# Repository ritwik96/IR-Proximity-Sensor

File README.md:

# IR-Proximity-Sensor
Tunable IR based proximity sensor with a digital output

<ul>
<li>Autodesk Eagle .brd and .sch files included with all non-standard libs</li>
<li>Sample Arduino code also for tuning and testing included</li>
<li>Potentiometer used to adjust the range</li>
<li>Detection range of about 9cm (3.5 in)</li>
</ul>
<p><strong>Important Notes:</strong></p>
<ul class="remarkup-list">
<li class="remarkup-list-item">The 220 &Omega; resistor is a pull-up in parallel with the LED. The LED needs to be one with an internal resistance (Standard RED 5mm LED with internal resistance is recommended)</li>
<li class="remarkup-list-item">The board has a normal HIGH and triggered LOW. The LED will be ON when the sensor hasn't been triggered and will turn OFF when it has.</li>
</ul>
<br>
<br>
<b> BOM: </b>
<table style="width: 340px;">
<tbody>
<tr>
<td style="width: 224px;">
<p><strong>Part</strong></p>
</td>
<td style="width: 90px;">
<p><strong>Part no.</strong></p>
</td>
<td style="width: 25px;">
<p><strong>Quantity</strong></p>
</td>
</tr>
<tr>
<td style="width: 224px;">
<p>IR Reflective Sensor</p>
</td>
<td style="width: 90px;">
<p>TCRT 5000</p>
</td>
<td style="width: 25px;">
<p>1</p>
</td>
</tr>
<tr>
<td style="width: 224px;">
<p>Red LED (internal resistor)</p>
</td>
<td style="width: 90px;">&nbsp;</td>
<td style="width: 25px;">
<p>1</p>
</td>
</tr>
<tr>
<td style="width: 224px;">
<p>100 ohm Resistor</p>
</td>
<td style="width: 90px;">&nbsp;</td>
<td style="width: 25px;">
<p>1</p>
</td>
</tr>
<tr>
<td style="width: 224px;">
<p>220 ohm Resistor</p>
</td>
<td style="width: 90px;">&nbsp;</td>
<td style="width: 25px;">
<p>1</p>
</td>
</tr>
<tr>
<td style="width: 224px;">
<p>4.7k ohm Resistor</p>
</td>
<td style="width: 90px;">&nbsp;</td>
<td style="width: 25px;">
<p>1</p>
</td>
</tr>
<tr>
<td style="width: 224px;">
<p>10k Multi-turn POT</p>
</td>
<td style="width: 90px;">&nbsp;</td>
<td style="width: 25px;">
<p>1</p>
</td>
</tr>
<tr>
<td style="width: 224px;">
<p>0.1uF Ceramic Capacitor</p>
</td>
<td style="width: 90px;">&nbsp;</td>
<td style="width: 25px;">
<p>2</p>
</td>
</tr>
<tr>
<td style="width: 224px;">
<p>TL081 op-amp</p>
</td>
<td style="width: 90px;">
<p>TL081</p>
</td>
<td style="width: 25px;">
<p>1</p>
</td>
</tr>
<tr>
<td style="width: 224px;">
<p>LM311N op-amp</p>
</td>
<td style="width: 90px;">
<p>LM311N</p>
</td>
<td style="width: 25px;">
<p>1</p>
</td>
</tr>
<tr>
<td style="width: 224px;">
<p>Break Away Headers</p>
</td>
<td style="width: 90px;">&nbsp;</td>
<td style="width: 25px;">
<p>6</p>
</td>
</tr>
</tbody>
</table>
<br>
<br>
<b> Schematic </b>
<p><img src="https://lh3.googleusercontent.com/fife/AAWUweXJ0cqJTT9yQKcJLtwWGiwWtPHNEDslHPKHX4X1kVe6rQgvylilLF-veRYypt4GBSyLvxIxgf_NBnjHtnxn2Fl2rCG9K_CXedOrj_bJrCb9PioXvAnjB80D2a0JiKlN0q2BV1EuuyBJM3cF4zWPFrK_ZCTCOgk6yfm_oHXbCRD5ekSx6PWZowFjhlelqWYi70vbxbF-7owTEbR0xGJ5UWBRVcrjVOpbwydnRtH584SyAf-udRqynxx5dkARvue_5rLb3AlWk1Whh5RAajTCkvgW4AK1EAxEA8O7RRdv5iY4lzVDs3q3AZRbzjtEcMSYzmWkkQL8p_EDrIesJH7LgoMswqbennmZJk6drwUTHa71WNQo625rHrt8JnTFp2NSJ6NUYdfE151DOkQJxdNym9DSvMmVbrnafRu51aJyEk-NZaPi9QqR9XVH6-emrRRxPwtjUv7AzXcPG-ChSayDAqQHkr3lHhr_HujkP6v8GJ7Ek8r4JnYpr-zAE-dVjSty9proRJBWXbD01yU5dkvpQ8BYxBlc7e2ec_te5tm6TB70sySlBcXVLOqPu8-fop8WtkFTbITsYDsc-INzU177CpvXsvYDvdM7-Vjdk6bKgADZnufWxZXwwVHX3nUWLGIkV43qQwWrHAA816nxQxJTwIUY5DzuLddsJ_GjRQXqQ61aT__i1tyuH3yLi4vK7uP3y0tMJPLedDnnJIhWBYNk91k-UWk83fL_AC7vRa7_l8D-C2yvENC-iwf1alsjptwYCByUk4cvoQbbeGjgenzsshzjy2SdnkBOlhW0RhNocaOOkBKnMzyLFkr0ULQ3GJD6mguxIJdqG7CRH68a-Pl1_XZ5OfUJI4QYMwJ18C_BT0NWODeldg-inMBEKxh29MLZ8zIS4MpJWytfc0aYgFdNBcCUETBavcrAqinttq3YfZGPw8WbIf54afK3jPAQjIfaGodGy0qtbEUKXmHyIePLx9rw3gC59Uip7NdncRc8NIJMqCAMtXVjI8OnZH58SrmUf0QIwZfzkkGyAQ264nmQQM5bM-25FlpJIfriYAnz6cHoLN6rQkTZCmzi7AUVCMAzfGevw9UFx7Adk3Q3j2fWAD78qvecGiyIZuXCTCXmhoCpCuhUNc9kRCWo-vuahQz9BENvtymh8kyJj-AwA9Niu45XOD043px8s4_OlvbjdNb-VAIlMGryZ3OectBs7BbqDaD0-c9xFugOCttM_4Tn2e-H8yTLttc1BWikI82273CD3G56k1ZH5o07MobdQc12tD5cWWRtP6IS_J6vC4gZEj-jM_8oDNllCH6MjUvSWEbnKAHjXu-avTNzrUCLkVz64DbCiiWOAUu60jM1AWN8OCly30CuyNWg2KreVKFh8v0ZTHyILAKf1MzP5oEXidUEEe-LI36NUuLEj9IOODJtNKK6oW2PpvOdvrH3tbwfAw5Af32BFiYyNrqu2490iqmG_BL2tslQMtXDjyu0mlZt9GxM8YzY6WgpfVl5zzp3Ih2lDolEXcSJTntM3rKIvmz7Bs_Khb9HHj3Y8v3xbcyiXVLvpdX2qNtXukv05Y8x05GDsp59mWwkrLJorkgG-Eh5kPmEPltWHlA2lcAxN1EQIZrs10f7ycuyMRtShH4vymmiTzteLxZle8fCAyBbxx_BmKJiU03YqFCQq2MoFFU43bGBEuxs20FnXFYBEQt2x9yrEJ94GQ16KcLWwIRsBsCuYT4ekjIKE8RHF7VOGT-ZcSkayg9mSYw3FODNxonVjNbYXlbvWIP0-sByOPo5AyfK6kWpGPndsg1T9ogEUTXN32a1CnleRyb_ccDMs5kaSVA_nfqZ7RreaXSj8PavfMwAv9ibYOmS0SjZ76zIcb0dIJC7D_SzT44zdXpMAAXEPWCfTBj6HfJVU3IbzwB8W1vevgtk9MoOuS0_nCHk6jJAUg4gvagi8ZMxVawoSxpBNMpRm28Lnk243cEJkULltNM3uga3nltLoyhNbtYhMlIXtQ7Uynx69zBnO-2WP8uNJpHhrF7ViGFTa2iSNq46iVgfaQIfewvbFprwMCFNRnXhkqi4X3cFJhdRqhqxQ4VhZ_7_kiT-fTb2esYIBMuvrr2P4dbOHbYCSA0XigmI8ZxShCH80p3EZVXWyqOzcscU1aXllhD9_zsxhFEfYV9_RS5KsZJbd3o2Ec1sdUKBxMyqP1GwGSXpZ4ZLdUcoTWYqwpNyDum7Q2kOOSPLw6GxMatMozznrZ5EloGHrwIsWk1-kS48AC1m5pTfynU5_iSSfHKHiVRbHZkbdDKxK1jBuIY_7CWebR24LIvnu7rDrFW3ja3GNWl0nijK6kEcOsZburlDmnHF5PWvipmcDeB1PaRPRv27cZ_jcRStsBskj8G3b_LXndvVsPCdjOi0cspqZTnuaBrDTk8G9HXWdVNmdyGpHz3Ij39iosXmOx6b9IHicOapG3gi66TEsfWLI5TWymjwoOYtgu11lSvmQ8XAyOE59gKGfkqQqcMi5Y--Yn-JpZoOBrEUrWF0Bxvk8nV8JKj7zd5kfAF8EUm7oR3ZjkH5Zzi6XRcYg_0LWSXXUcvvfavBZ_tg5wkFAnvQhUCoKLwnwAzZ8ho7QcQqebX-oYHcC7H4xqhHQml6nVDzq10h-OW1bn6iEUdtnieh2t-XhsPU8inyDsLDXPGjxMwk0GQ7j7zSqqXEZ0vtoNj2L8FhlF7c8SqGAgr1V40fJ75NzGhh5YI6OgI5LU_tAEVD660-H5bLWilHTutoy1x5QcCBnYMkflmBZncyOvV7DAD3C-GpSIRoY_x03-QP7-zb9kU5eqQiaPZ7YacrJrV2fWEpkhlo4fCg94JbSs56TnGDfXyFFSZv2d5ac6ALYDgplpE9p-jO_yEZuaS-3s2vvIv-s0dyr9C9rxdgmDMKFjdu_gYxSxPKvkPt-6RfwBZr_oc2XGWyHa3p2zFBTFMq0-DWxPfRgVStAohx1Jpsf1qm-jojxymwdm6uh4rAaWW8D1k34AwaKNlLLgw7pDEiYhbJ024qaizds4lOaSaTKW_PaZ90YwLfmIMPPjgN6w_1zjpqy2DH5z4W58V2XWqP61jftZGEcTaNVKAFMrDhaEXu9Ci61uHg_mdKuGijvg9YBQ0_bZ54lZzhfwcDKjpvBDrDEJr870M1SQExzMBFYDZnU-SFbDZDJL5S5v_HpecCahdA0B5WCgoM7-a9yIHPB6DK42S2TvEf1NXwhL6kjnIT14togUgFT_iuqBD7CkOdjLLcFgf454nLscb8B00Sr9Py-33zWfD3NAGlp3gqtaCCl8ofj-StlHzvCU_Z1KRBiQp68_YE5GxzGvlXZFchUZ2icvXA1jWsCENTQn5ZYCjmTCs6w6doq4zc920_wFd1tZMGv-W_TVxMNSX5_0FuN92mXZTSgJIEq3iblNqKbhZYgA68q5mH0813hcS2ONU1bTXb0YXwkvN99FQpDCiOrtdzcj2RaYH2H7yjopAJ-oOjUFOfaiYmB8JnOx6vDSz0GFBucXswOS-Nemzfz42at4rRRXstm_Brjpf2JPLOQwLGUMwl3XYddlAuryTyxJRtG6p-PUj6-YTrhXj4T6WAhjYmgmNOSm-tp7lyQMKebPg7mVqkZNuU8BppvTwsWTiYJUZqLAKt7ivGpPlBkWxmu8bcEwQEU_JFWgT3aZRKv9lIUwJGAWt_uyAQIdN3AzPeVnhNBbtF-yrrhxbGd-SLLOiQx61h5ioc86I=s1490-w1490-h647-no" alt="Schematic" /></p>
<br>
<br>
<b> Prototype Board </b>
<p><img src="https://lh3.googleusercontent.com/cFEWzSny9ccC4d_HE8IASWJgXHdl8u-RXzT_TEeWNE-iyhfp9NyLiTfxM5cJoXSZFosWdKZK19vt2ZbRmecgdbaDPPTemqoxb_MeuwmrncJQosgrSmDAabYzOnkEWu5S71KXQWYxnUMIoJl2BU42n01tZPTwKhygag0Ah5SI-17bRR5-WfLz98OFMJ9k_4bPc5eQliZjYWnFDLH_yLVeKES1i7ADf73Vw7brMtxizSIqGZGDEDDAC_2KqrW0WDPaQWnvs8fKQRUDVmUdQQZCCnBNx0QURYSv3gcTCw5eWjwKbgeOhaQIKIB9rrFHgLp58OWtYXJ1Kn1otXfOdVWdYpw0dYs72Cz2Dkwp6EsakRoGNUfZPEtYTr5ZIsj9JJXoKF6XW177EasanWhQxZd-pF7RDV26Kp1ka3C2I1JXXKzWI9bvU3ZtQzG8rOKhkmgYDLj8k1KykYC95zMy82bFdjvPdJZCyRuDCZB6zWf6wEUW_k6uyYwG-nZB6ZenEomgcwrsLf5R2AjF9PllFyK5QEX1MTJLFMRy6Qw-oMzNSP1f3y-DtuQaWvH4AKCNpF_8nBOqh3PW7A2jpOMLACG651VI3dmTwqCpfSbSWzr6lGeBDKGozDUCNh0TFBc6JjV4ARjUFRYOKu3Aq7q0RJVWL69sonvdUf18zGPUgIp8uMwbDEguyBHpM-7cXxcYNbzXNUAWLd-XN-qKLZO5nLM43Hwf=s975-no" alt="Prototype Board" /></p>
<br>
<br>
<b> BreadBoard based testing </b>
<p><img src="https://lh3.googleusercontent.com/KNCvc36VUrslMxsh6HmgmDm3YOIE5rriZh35m3Jh_tQKE1vIxncJQ9UeL9BvH72-x3cRnJxBT2OJ4o7zHGsv2hv3hWVHML6OwoHX1cR3RLsXQI-MtN4q6jbs-hKA7ZZLTGPMRexm3vYKevmCRJZUkNi4ts5JK7wZM2hLY7YpQzJQBDPNLCaAP7MQbGGfoDwEiQckH-RjEJ4XxpLdGNfTUuMhU54wYxUS-FlFjFhMGsDZgHqHCAHEc0aoSaTx-h17VHzn1e0oY7mCy3YJzWBKXtKah7L0en7N_McKMPbu4eX3CoaNEb1K7cpucCAF76_R7e36YmtOPG93sDLarWv7YCSUDajd-rbAE0PWDB91UlcSK-ZMoHE6HF1Q0rOrWRyfEBs9J1Sqe5gSUBvAy0oLEHeemQyq8Ofhw_mydzcYbB_g4xJTV0_fafTNZgmjg38GIcKKTAWLCjsJPOeMuOfzhm5h1X0OvZtVLoGM-YD9ig2uoD5o5zgkX6odojuREnOgi6ZC5FekFVk2FhQ6Jpvy9MeC8vPvBywArM6KvpoCqKN9lV6OcufxVvlg9nMkm8s-I5VU2qhFYb5vx1Ge6IOx6vHoRnC7CPWiHc-CvKhJ2RlDyhEP3VXrD1ZRANMmraztDeo6BIafrkpeM3lvhzD2DIAcsEXcpVTKwZYM0w-uEAE0v4EDGa73ulXWzAkUJXIuE8NhkAklDUBo9MHXvhtkclR4=w1300-h975-no" alt="Prototype Board" /></p>
<br>
<br>

OSH Park Project Link: <a href="https://oshpark.com/shared_projects/O8bRqG8g"></img></a>

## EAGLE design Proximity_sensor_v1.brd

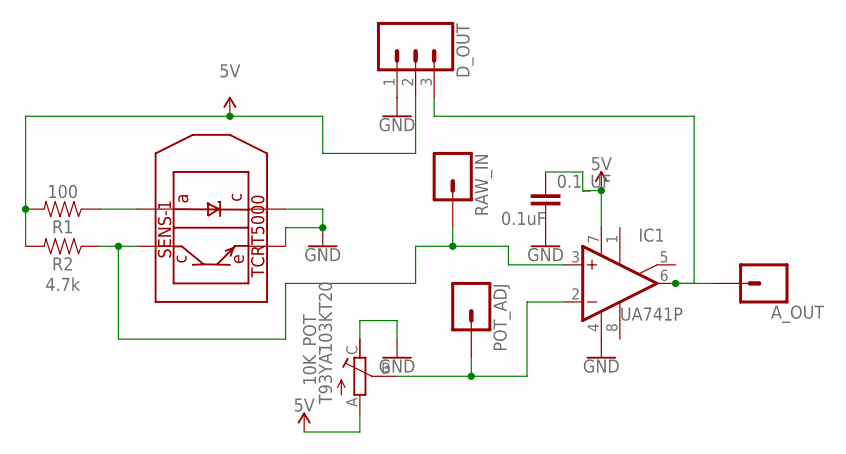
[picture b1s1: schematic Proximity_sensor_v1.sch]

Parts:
0.1_UF: 0.1uF; CAP-PTH-SMALL-KIT
10K_POT: T93YA103KT20; TRIM_T93YA103KT20
A_OUT: CONN_01; 1X01
D_OUT: CONN_03; 1X03
IC1: UA741P; DIL08
POT_ADJ: CONN_01; 1X01
R1: 100; AXIAL-0.3-KIT
R2: 4.7k; AXIAL-0.3-KIT
RAW_IN: CONN_01; 1X01
SENS-1: TCRT5000; 5000

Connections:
5V: 0.1_UF.1, 10K_POT.A, D_OUT.2, IC1.7 (V+), R1.P$2 (2), R2.P$2 (2)
GND: 0.1_UF.2, 10K_POT.C, D_OUT.1, IC1.4 (V-), SENS-1.P$2, SENS-1.P$4
unnamed: R1.P$1 (1), SENS-1.P$3
unnamed: 10K_POT.B, IC1.2 (-IN), POT_ADJ.1
unnamed: A_OUT.1, D_OUT.3, IC1.6 (OUT)
unnamed: IC1.3 (+IN), R2.P$1 (1), RAW_IN.1, SENS-1.P$1

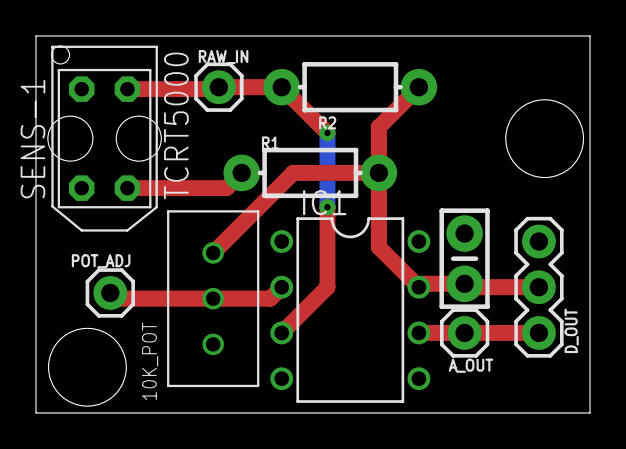
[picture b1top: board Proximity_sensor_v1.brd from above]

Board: 2 copper layers, 30.8 x 20.9 mm, 10 parts (0 on the bottom side), 6 nets.

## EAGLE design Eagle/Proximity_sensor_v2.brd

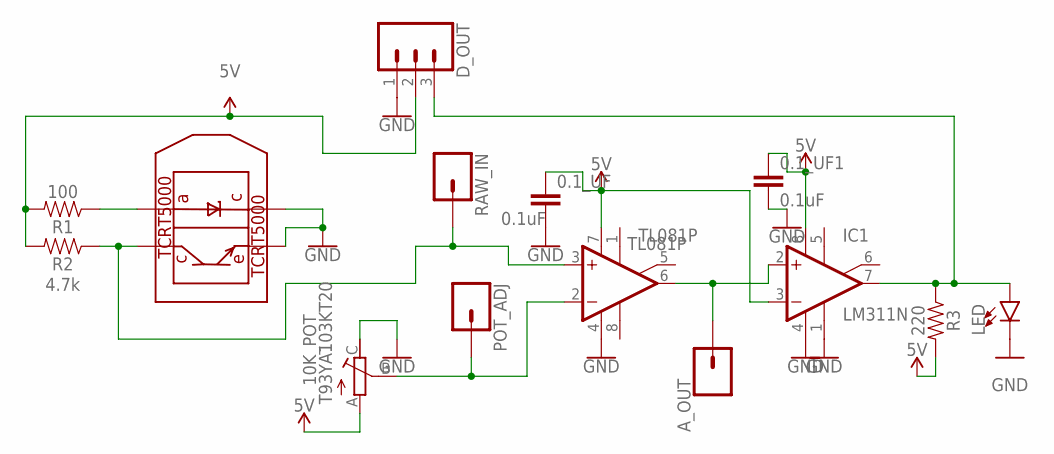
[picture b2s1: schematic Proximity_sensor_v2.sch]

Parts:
0.1_UF, 0.1_UF1: 0.1uF; CAP-PTH-SMALL-KIT
10K_POT: T93YA103KT20; TRIM_T93YA103KT20
A_OUT: CONN_01; 1X01
D_OUT: CONN_03; 1X03
IC1: LM311N; DIL08
LED: LED5MM; LED_5MM
POT_ADJ: CONN_01; 1X01
R1: 100; AXIAL-0.3-KIT
R2: 4.7k; AXIAL-0.3-KIT
R3: 220; AXIAL-0.3-KIT
RAW_IN: CONN_01; 1X01
TCRT5000: TCRT5000; 5000
TL081P: TL081P; DIL08

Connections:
5V: 0.1_UF.1, 0.1_UF1.1, 10K_POT.A, D_OUT.2, IC1.3 (-IN), IC1.8 (V+), R1.P$2 (2), R2.P$2 (2), R3.P$2 (2), TL081P.7 (V+)
A_OUT: A_OUT.1, IC1.2 (+IN), TL081P.6 (OUT)
GND: 0.1_UF.2, 0.1_UF1.2, 10K_POT.C, D_OUT.1, IC1.1 (GND), IC1.4 (V-), LED.K (C), TCRT5000.P$2, TCRT5000.P$4, TL081P.4 (V-)
OUTPUT: D_OUT.3, IC1.7 (OUT), LED.A, R3.P$1 (1)
RAW: R2.P$1 (1), RAW_IN.1, TCRT5000.P$1, TL081P.3 (+IN)
REF: 10K_POT.B, POT_ADJ.1, TL081P.2 (-IN)
SOURCING: R1.P$1 (1), TCRT5000.P$3

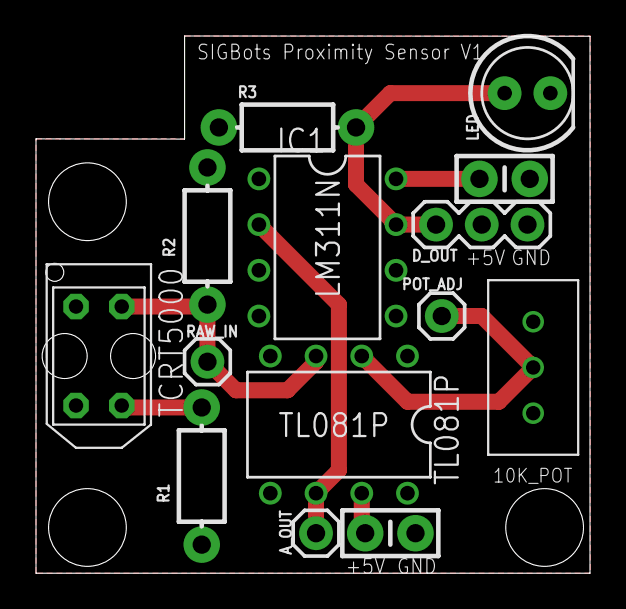
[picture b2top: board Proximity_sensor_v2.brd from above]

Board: 2 copper layers, 30.8 x 29.8 mm, 14 parts (0 on the bottom side), 7 nets.

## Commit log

2019-03-21 Add files via upload
    Gives a serial output that can be graphed

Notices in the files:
parts and their libraries:
SparkFun-Connectors: Licensing: Creative Commons ShareAlike 4.0 International - https://creativecommons.org/licenses/by-sa/4.0
